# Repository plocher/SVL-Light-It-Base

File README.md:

# SVL-Light-It-Base
## License: CERN Open Hardware Licence v1.2

first line is a description of SVL-Light-It-Base

the rest of the file is a longer description

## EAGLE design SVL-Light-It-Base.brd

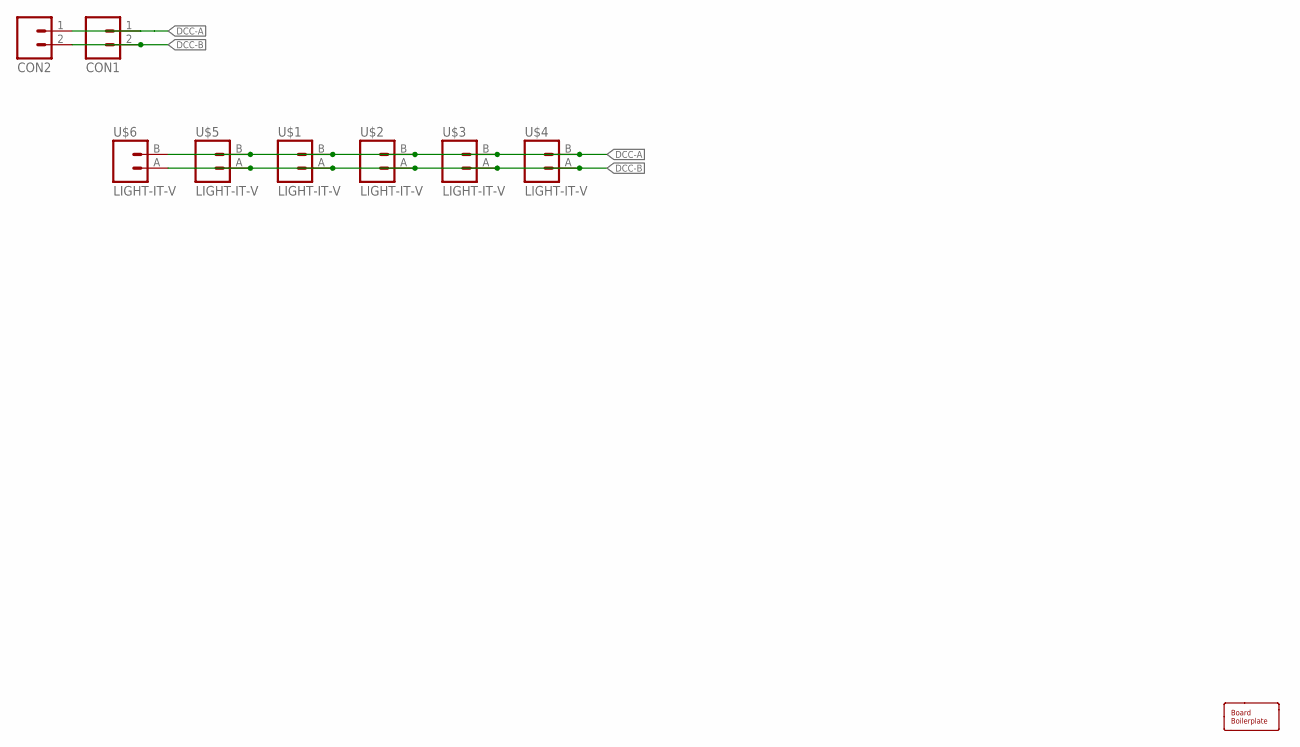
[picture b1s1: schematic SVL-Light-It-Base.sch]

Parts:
BOARD1: BOARD100X100; BOARD-SEEED10X10
CON1, CON2: CONNECTOR-M02508-LOCK; MSTB2
U$1, U$2, U$3, U$4, U$5, U$6: LIGHT-IT-V

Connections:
DCC-A: CON1.1 (A), CON2.1 (A), U$1.B, U$2.B, U$3.B, U$4.B, U$5.B, U$6.B
DCC-B: CON1.2 (B), CON2.2 (B), U$1.A, U$2.A, U$3.A, U$4.A, U$5.A, U$6.A

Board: 2 copper layers, 9 parts (0 on the bottom side), 2 nets, no tracks yet.

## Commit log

2020-05-04 updated tags
2020-09-19 Obsolete
